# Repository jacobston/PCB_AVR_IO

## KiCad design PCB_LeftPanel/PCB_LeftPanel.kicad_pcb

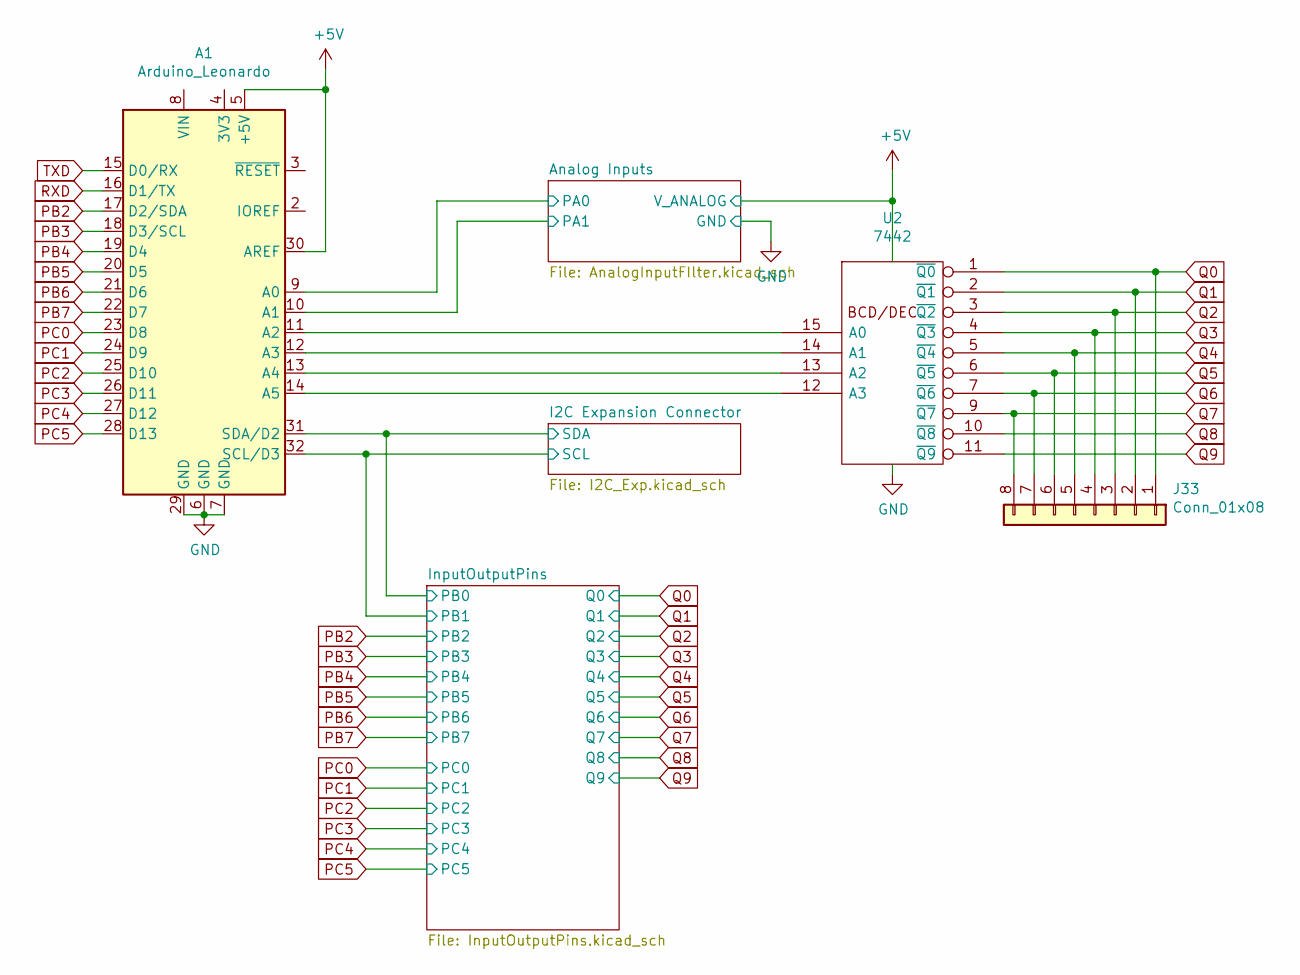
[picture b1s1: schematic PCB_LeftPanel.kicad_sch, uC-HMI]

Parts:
A1: Arduino_Leonardo; Arduino_UNO_R3
J33: Conn_01x08; PinHeader_1x08_P2.54mm_Vertical
U2: 7442; DIP-16_W7.62mm

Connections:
+5V: A1.5 (+5V), A1.30 (AREF), U2.16 (VCC); also elsewhere on the board
/Analog Inputs/PA0: A1.9 (A0); also elsewhere on the board
/Analog Inputs/PA1: A1.10 (A1); also elsewhere on the board
/I2C Expansion Connector/SCL: A1.32 (SCL/D3); also elsewhere on the board
/I2C Expansion Connector/SDA: A1.31 (SDA/D2); also elsewhere on the board
GND: A1.6 (GND), A1.7 (GND), A1.29 (GND), U2.8 (GND); also elsewhere on the board
unnamed: A1.11 (A2), U2.15 (A0)
unnamed: A1.12 (A3), U2.14 (A1)
unnamed: A1.13 (A4), U2.13 (A2)
unnamed: A1.14 (A5), U2.12 (A3)
PB2: A1.17 (D2/SDA); also elsewhere on the board
PB3: A1.18 (D3/SCL); also elsewhere on the board
PB4: A1.19 (D4); also elsewhere on the board
PB5: A1.20 (D5); also elsewhere on the board
PB6: A1.21 (D6); also elsewhere on the board
PB7: A1.22 (D7); also elsewhere on the board
PC0: A1.23 (D8); also elsewhere on the board
PC1: A1.24 (D9); also elsewhere on the board
PC2: A1.25 (D10); also elsewhere on the board
PC3: A1.26 (D11); also elsewhere on the board
PC4: A1.27 (D12); also elsewhere on the board
PC5: A1.28 (D13); also elsewhere on the board
Q0: J33.1, U2.1 (~Q0); also elsewhere on the board
Q1: J33.2, U2.2 (~Q1); also elsewhere on the board
Q2: J33.3, U2.3 (~Q2); also elsewhere on the board
Q3: J33.4, U2.4 (~Q3); also elsewhere on the board
Q4: J33.5, U2.5 (~Q4); also elsewhere on the board
Q5: J33.6, U2.6 (~Q5); also elsewhere on the board
Q6: J33.7, U2.7 (~Q6); also elsewhere on the board
Q7: J33.8, U2.9 (~Q7); also elsewhere on the board
Q8: U2.10 (~Q8); also elsewhere on the board
Q9: U2.11 (~Q9); also elsewhere on the board
RXD: A1.16 (D1/TX); also elsewhere on the board
TXD: A1.15 (D0/RX); also elsewhere on the board

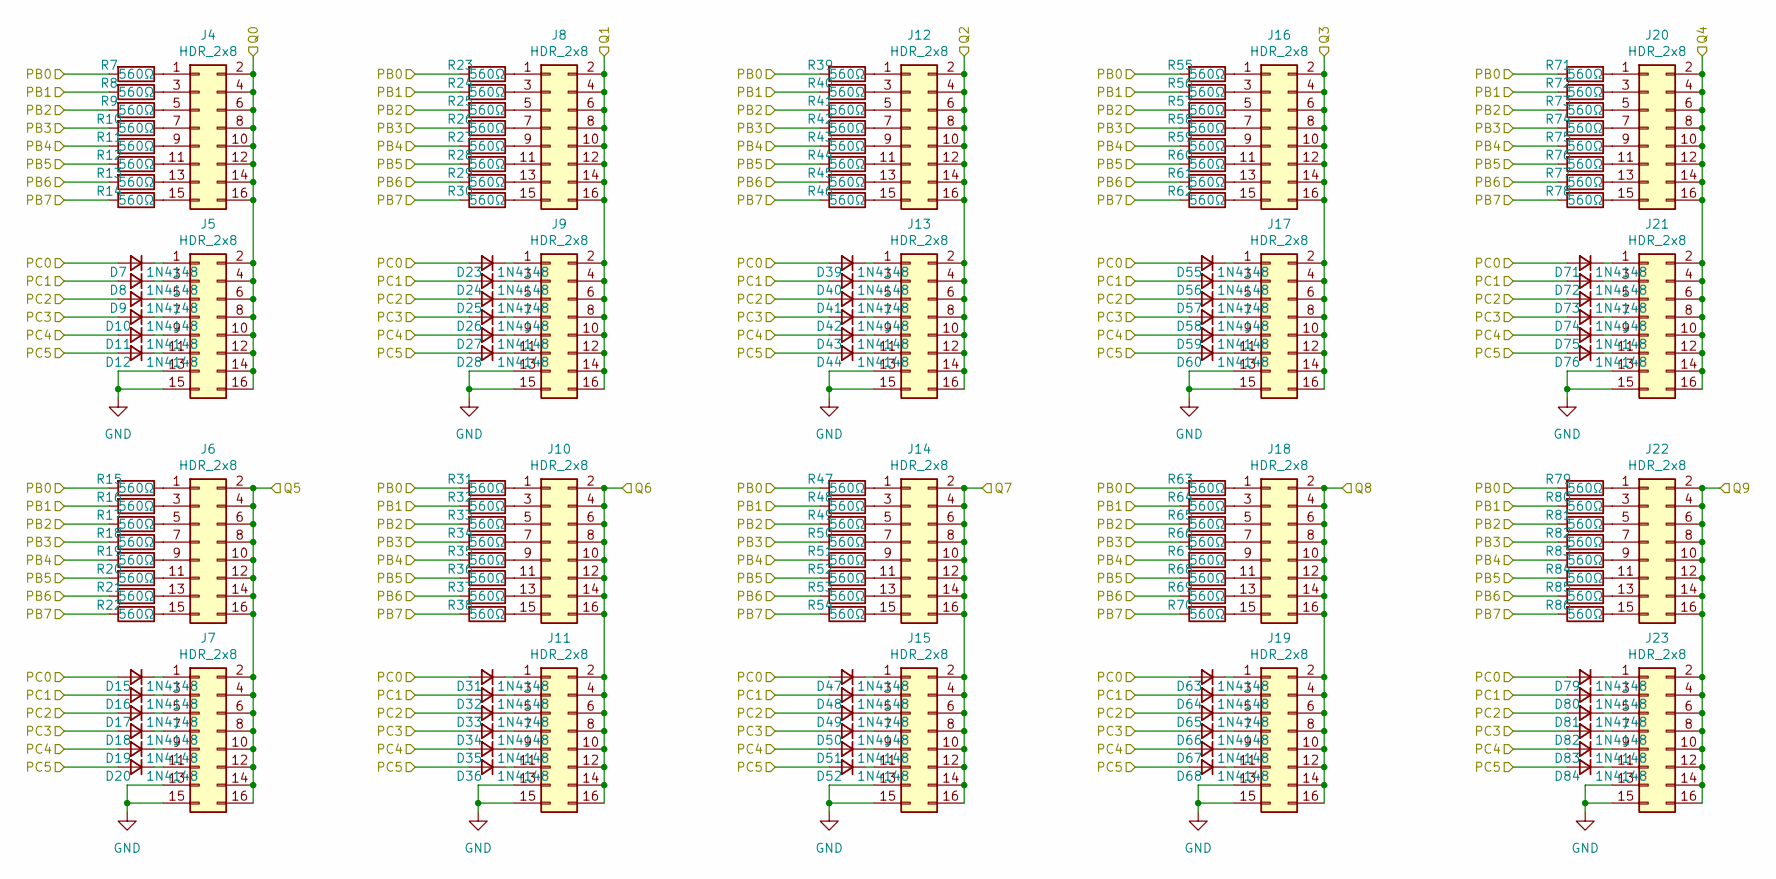
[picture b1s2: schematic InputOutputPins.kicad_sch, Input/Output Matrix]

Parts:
D7, D8, D9, D10, D11, D12, D15, D16, D17, D18, D19, D20, D23, D24, D25, D26, D27, D28, D31, D32, D33, D34, D35, D36, D39, D40, D41, D42, D43, D44, D47, D48, D49, D50, D51, D52, D55, D56, D57, D58, D59, D60, D63, D64, D65, D66, D67, D68, D71, D72, D73, D74, D75, D76, D79, D80, D81, D82, D83, D84: 1N4148; D_DO-35_SOD27_P7.62mm_Horizontal
J4, J5, J6, J7, J8, J9, J10, J11, J12, J13, J14, J15, J16, J17, J18, J19, J20, J21, J22, J23: HDR_2x8; PinHeader_2x08_P2.54mm_Vertical
R7, R8, R9, R10, R11, R12, R13, R14, R15, R16, R17, R18, R19, R20, R21, R22, R23, R24, R25, R26, R27, R28, R29, R30, R31, R32, R33, R34, R35, R36, R37, R38, R39, R40, R41, R42, R43, R44, R45, R46, R47, R48, R49, R50, R51, R52, R53, R54, R55, R56, R57, R58, R59, R60, R61, R62, R63, R64, R65, R66, R67, R68, R69, R70, R71, R72, R73, R74, R75, R76, R77, R78, R79, R80, R81, R82, R83, R84, R85, R86: 560Ω; R_Axial_DIN0204_L3.6mm_D1.6mm_P7.62mm_Horizontal

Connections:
/I2C Expansion Connector/SCL: R8.2, R16.2, R24.2, R32.2, R40.2, R48.2, R56.2, R64.2, R72.2, R80.2; also elsewhere on the board
/I2C Expansion Connector/SDA: R7.2, R15.2, R23.2, R31.2, R39.2, R47.2, R55.2, R63.2, R71.2, R79.2; also elsewhere on the board
GND: J5.13, J5.15, J7.13, J7.15, J9.13, J9.15, J11.13, J11.15, J13.13, J13.15, J15.13, J15.15, J17.13, J17.15, J19.13, J19.15, J21.13, J21.15, J23.13, J23.15; also elsewhere on the board
unnamed: D7.1 (K), J5.1
unnamed: D8.1 (K), J5.3
unnamed: D9.1 (K), J5.5
unnamed: D10.1 (K), J5.7
unnamed: D11.1 (K), J5.9
unnamed: D12.1 (K), J5.11
unnamed: D15.1 (K), J7.1
unnamed: D16.1 (K), J7.3
unnamed: D17.1 (K), J7.5
unnamed: D18.1 (K), J7.7
unnamed: D19.1 (K), J7.9
unnamed: D20.1 (K), J7.11
unnamed: D23.1 (K), J9.1
unnamed: D24.1 (K), J9.3
unnamed: D25.1 (K), J9.5
unnamed: D26.1 (K), J9.7
unnamed: D27.1 (K), J9.9
unnamed: D28.1 (K), J9.11
unnamed: D31.1 (K), J11.1
unnamed: D32.1 (K), J11.3
unnamed: D33.1 (K), J11.5
unnamed: D34.1 (K), J11.7
unnamed: D35.1 (K), J11.9
unnamed: D36.1 (K), J11.11
unnamed: D39.1 (K), J13.1
unnamed: D40.1 (K), J13.3
unnamed: D41.1 (K), J13.5
unnamed: D42.1 (K), J13.7
unnamed: D43.1 (K), J13.9
unnamed: D44.1 (K), J13.11
unnamed: D47.1 (K), J15.1
unnamed: D48.1 (K), J15.3
unnamed: D49.1 (K), J15.5
unnamed: D50.1 (K), J15.7
unnamed: D51.1 (K), J15.9
unnamed: D52.1 (K), J15.11
unnamed: D55.1 (K), J17.1
unnamed: D56.1 (K), J17.3
unnamed: D57.1 (K), J17.5
unnamed: D58.1 (K), J17.7
unnamed: D59.1 (K), J17.9
unnamed: D60.1 (K), J17.11
unnamed: D63.1 (K), J19.1
unnamed: D64.1 (K), J19.3
unnamed: D65.1 (K), J19.5
unnamed: D66.1 (K), J19.7
unnamed: D67.1 (K), J19.9
unnamed: D68.1 (K), J19.11
unnamed: D71.1 (K), J21.1
unnamed: D72.1 (K), J21.3
unnamed: D73.1 (K), J21.5
unnamed: D74.1 (K), J21.7
unnamed: D75.1 (K), J21.9
unnamed: D76.1 (K), J21.11
unnamed: D79.1 (K), J23.1
unnamed: D80.1 (K), J23.3
unnamed: D81.1 (K), J23.5
unnamed: D82.1 (K), J23.7
unnamed: D83.1 (K), J23.9
unnamed: D84.1 (K), J23.11
unnamed: J4.1, R7.1
unnamed: J4.3, R8.1
unnamed: J4.5, R9.1
unnamed: J4.7, R10.1
unnamed: J4.9, R11.1
unnamed: J4.11, R12.1
unnamed: J4.13, R13.1
unnamed: J4.15, R14.1
unnamed: J6.1, R15.1
unnamed: J6.3, R16.1
unnamed: J6.5, R17.1
unnamed: J6.7, R18.1
unnamed: J6.9, R19.1
unnamed: J6.11, R20.1
unnamed: J6.13, R21.1
unnamed: J6.15, R22.1
unnamed: J8.1, R23.1
unnamed: J8.3, R24.1
unnamed: J8.5, R25.1
unnamed: J8.7, R26.1
unnamed: J8.9, R27.1
unnamed: J8.11, R28.1
unnamed: J8.13, R29.1
unnamed: J8.15, R30.1
unnamed: J10.1, R31.1
unnamed: J10.3, R32.1
unnamed: J10.5, R33.1
unnamed: J10.7, R34.1
unnamed: J10.9, R35.1
unnamed: J10.11, R36.1
unnamed: J10.13, R37.1
unnamed: J10.15, R38.1
unnamed: J12.1, R39.1
unnamed: J12.3, R40.1
unnamed: J12.5, R41.1
unnamed: J12.7, R42.1
unnamed: J12.9, R43.1
unnamed: J12.11, R44.1
unnamed: J12.13, R45.1
unnamed: J12.15, R46.1
unnamed: J14.1, R47.1
unnamed: J14.3, R48.1
unnamed: J14.5, R49.1
unnamed: J14.7, R50.1
unnamed: J14.9, R51.1
unnamed: J14.11, R52.1
unnamed: J14.13, R53.1
unnamed: J14.15, R54.1
unnamed: J16.1, R55.1
unnamed: J16.3, R56.1
unnamed: J16.5, R57.1
unnamed: J16.7, R58.1
unnamed: J16.9, R59.1
unnamed: J16.11, R60.1
unnamed: J16.13, R61.1
unnamed: J16.15, R62.1
unnamed: J18.1, R63.1
unnamed: J18.3, R64.1
unnamed: J18.5, R65.1
unnamed: J18.7, R66.1
unnamed: J18.9, R67.1
unnamed: J18.11, R68.1
unnamed: J18.13, R69.1
unnamed: J18.15, R70.1
unnamed: J20.1, R71.1
unnamed: J20.3, R72.1
unnamed: J20.5, R73.1
unnamed: J20.7, R74.1
unnamed: J20.9, R75.1
unnamed: J20.11, R76.1
unnamed: J20.13, R77.1
unnamed: J20.15, R78.1
unnamed: J22.1, R79.1
unnamed: J22.3, R80.1
unnamed: J22.5, R81.1
unnamed: J22.7, R82.1
unnamed: J22.9, R83.1
unnamed: J22.11, R84.1
unnamed: J22.13, R85.1
unnamed: J22.15, R86.1
PB2: R9.2, R17.2, R25.2, R33.2, R41.2, R49.2, R57.2, R65.2, R73.2, R81.2; also elsewhere on the board
PB3: R10.2, R18.2, R26.2, R34.2, R42.2, R50.2, R58.2, R66.2, R74.2, R82.2; also elsewhere on the board
PB4: R11.2, R19.2, R27.2, R35.2, R43.2, R51.2, R59.2, R67.2, R75.2, R83.2; also elsewhere on the board
PB5: R12.2, R20.2, R28.2, R36.2, R44.2, R52.2, R60.2, R68.2, R76.2, R84.2; also elsewhere on the board
PB6: R13.2, R21.2, R29.2, R37.2, R45.2, R53.2, R61.2, R69.2, R77.2, R85.2; also elsewhere on the board
PB7: R14.2, R22.2, R30.2, R38.2, R46.2, R54.2, R62.2, R70.2, R78.2, R86.2; also elsewhere on the board
PC0: D7.2 (A), D15.2 (A), D23.2 (A), D31.2 (A), D39.2 (A), D47.2 (A), D55.2 (A), D63.2 (A), D71.2 (A), D79.2 (A); also elsewhere on the board
PC1: D8.2 (A), D16.2 (A), D24.2 (A), D32.2 (A), D40.2 (A), D48.2 (A), D56.2 (A), D64.2 (A), D72.2 (A), D80.2 (A); also elsewhere on the board
PC2: D9.2 (A), D17.2 (A), D25.2 (A), D33.2 (A), D41.2 (A), D49.2 (A), D57.2 (A), D65.2 (A), D73.2 (A), D81.2 (A); also elsewhere on the board
PC3: D10.2 (A), D18.2 (A), D26.2 (A), D34.2 (A), D42.2 (A), D50.2 (A), D58.2 (A), D66.2 (A), D74.2 (A), D82.2 (A); also elsewhere on the board
PC4: D11.2 (A), D19.2 (A), D27.2 (A), D35.2 (A), D43.2 (A), D51.2 (A), D59.2 (A), D67.2 (A), D75.2 (A), D83.2 (A); also elsewhere on the board
PC5: D12.2 (A), D20.2 (A), D28.2 (A), D36.2 (A), D44.2 (A), D52.2 (A), D60.2 (A), D68.2 (A), D76.2 (A), D84.2 (A); also elsewhere on the board
Q0: J4.2, J4.4, J4.6, J4.8, J4.10, J4.12, J4.14, J4.16, J5.2, J5.4, J5.6, J5.8, J5.10, J5.12, J5.14, J5.16; also elsewhere on the board
Q1: J8.2, J8.4, J8.6, J8.8, J8.10, J8.12, J8.14, J8.16, J9.2, J9.4, J9.6, J9.8, J9.10, J9.12, J9.14, J9.16; also elsewhere on the board
Q2: J12.2, J12.4, J12.6, J12.8, J12.10, J12.12, J12.14, J12.16, J13.2, J13.4, J13.6, J13.8, J13.10, J13.12, J13.14, J13.16; also elsewhere on the board
Q3: J16.2, J16.4, J16.6, J16.8, J16.10, J16.12, J16.14, J16.16, J17.2, J17.4, J17.6, J17.8, J17.10, J17.12, J17.14, J17.16; also elsewhere on the board
Q4: J20.2, J20.4, J20.6, J20.8, J20.10, J20.12, J20.14, J20.16, J21.2, J21.4, J21.6, J21.8, J21.10, J21.12, J21.14, J21.16; also elsewhere on the board
Q5: J6.2, J6.4, J6.6, J6.8, J6.10, J6.12, J6.14, J6.16, J7.2, J7.4, J7.6, J7.8, J7.10, J7.12, J7.14, J7.16; also elsewhere on the board
Q6: J10.2, J10.4, J10.6, J10.8, J10.10, J10.12, J10.14, J10.16, J11.2, J11.4, J11.6, J11.8, J11.10, J11.12, J11.14, J11.16; also elsewhere on the board
Q7: J14.2, J14.4, J14.6, J14.8, J14.10, J14.12, J14.14, J14.16, J15.2, J15.4, J15.6, J15.8, J15.10, J15.12, J15.14, J15.16; also elsewhere on the board
Q8: J18.2, J18.4, J18.6, J18.8, J18.10, J18.12, J18.14, J18.16, J19.2, J19.4, J19.6, J19.8, J19.10, J19.12, J19.14, J19.16; also elsewhere on the board
Q9: J22.2, J22.4, J22.6, J22.8, J22.10, J22.12, J22.14, J22.16, J23.2, J23.4, J23.6, J23.8, J23.10, J23.12, J23.14, J23.16; also elsewhere on the board

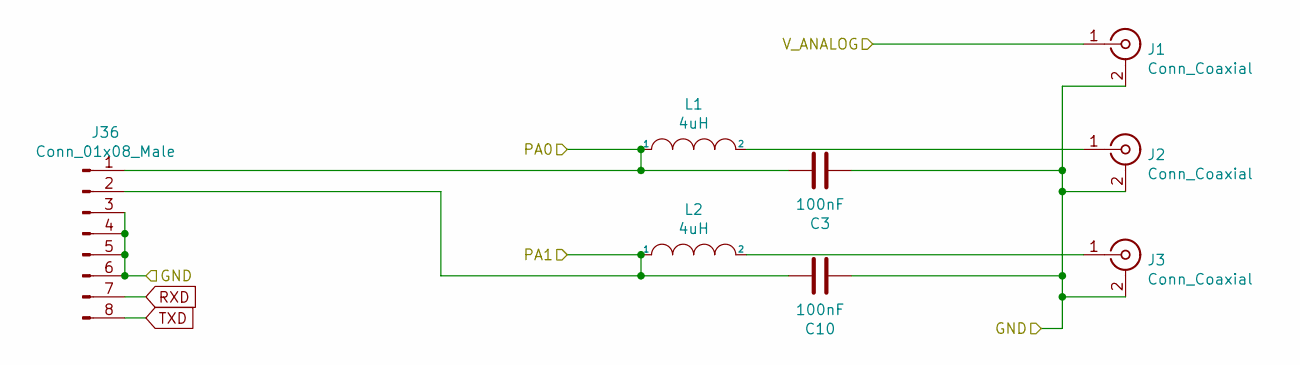
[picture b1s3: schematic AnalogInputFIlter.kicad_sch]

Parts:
C3, C10: 100nF; CP_Radial_D8.0mm_P5.00mm
J1, J2, J3: Conn_Coaxial; SMA_Amphenol_132203-12_Horizontal
J36: Conn_01x08_Male; PinHeader_1x08_P2.54mm_Vertical
L1, L2: 4uH; L_Axial_L5.0mm_D3.6mm_P10.00mm_Horizontal_Murata_BL01RN1A2A2

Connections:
+5V: J1.1 (In); also elsewhere on the board
/Analog Inputs/PA0: C3.1, J36.1, L1.1; also elsewhere on the board
/Analog Inputs/PA1: C10.1, J36.2, L2.1; also elsewhere on the board
GND: C3.2, C10.2, J1.2 (Ext), J2.2 (Ext), J3.2 (Ext), J36.3, J36.4, J36.5, J36.6; also elsewhere on the board
unnamed: J2.1 (In), L1.2
unnamed: J3.1 (In), L2.2
RXD: J36.7; also elsewhere on the board
TXD: J36.8; also elsewhere on the board

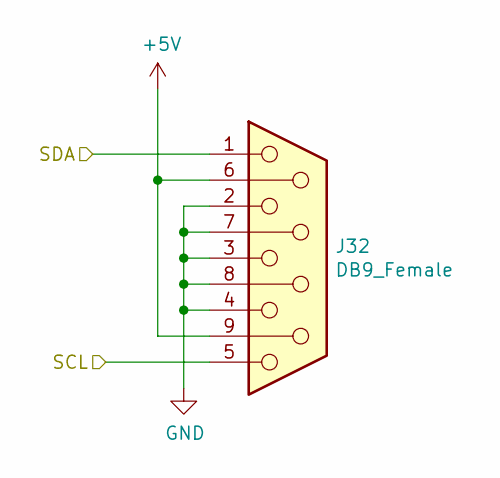
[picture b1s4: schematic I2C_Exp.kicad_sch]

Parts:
J32: DB9_Female; DSUB-9_Female_Vertical_P2.77x2.84mm_MountingHoles

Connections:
+5V: J32.6, J32.9; also elsewhere on the board
/I2C Expansion Connector/SCL: J32.5; also elsewhere on the board
/I2C Expansion Connector/SDA: J32.1; also elsewhere on the board
GND: J32.2, J32.3, J32.4, J32.7, J32.8; also elsewhere on the board

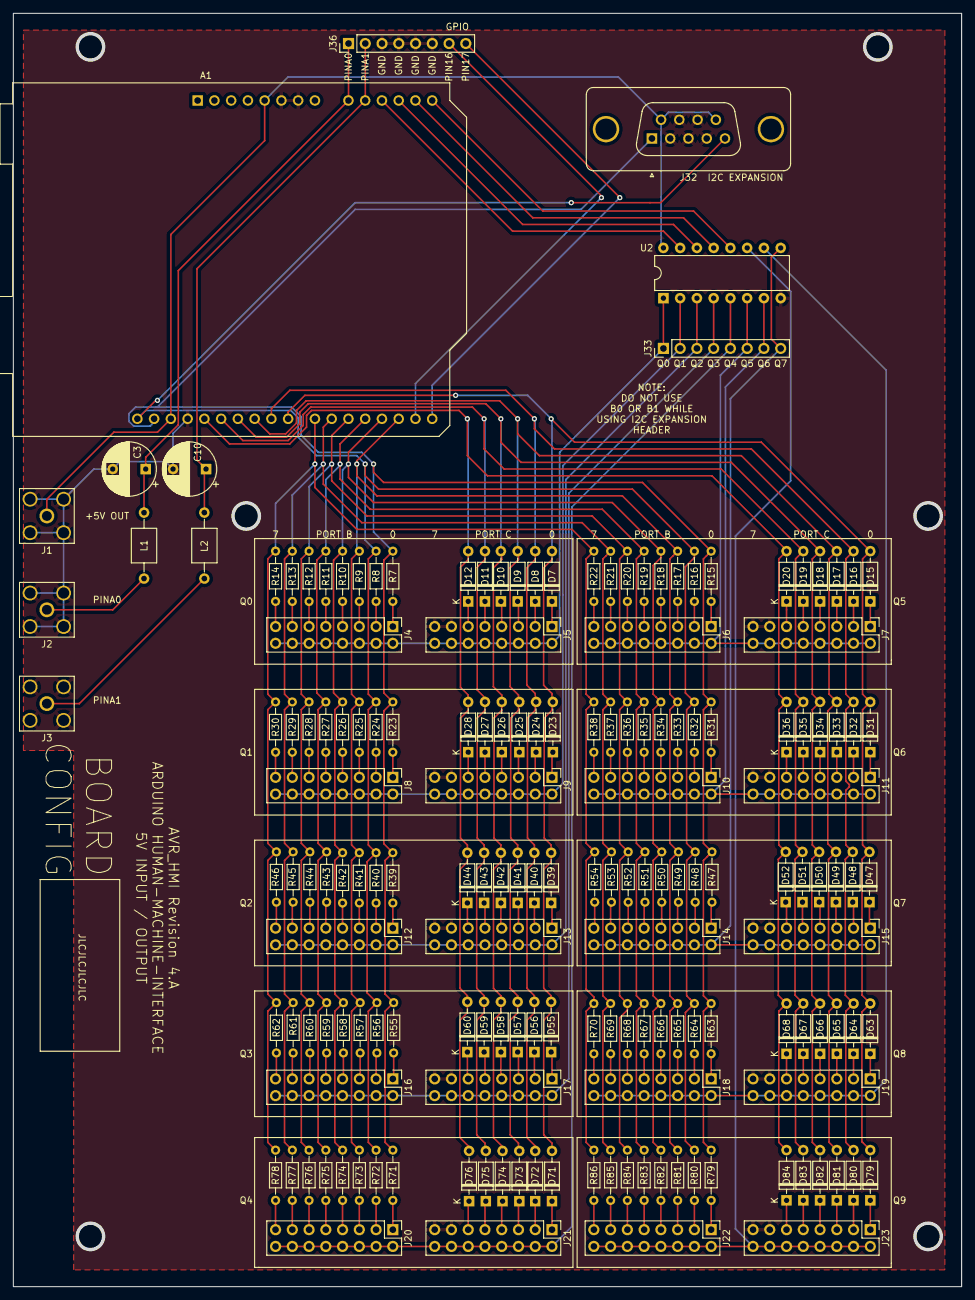
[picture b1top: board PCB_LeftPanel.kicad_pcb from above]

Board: 2 copper layers, 143.8 x 193.0 mm, 172 parts (0 on the bottom side), 176 nets.

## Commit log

2021-09-17 Add files via upload
    KiCAD files added to repository
2021-11-05 Rev.1 Upload
    Initial completed release
2023-03-25 Add files via upload
    Update to Revision 4.A
    Board now based on Arduino Leonardo / Uno
